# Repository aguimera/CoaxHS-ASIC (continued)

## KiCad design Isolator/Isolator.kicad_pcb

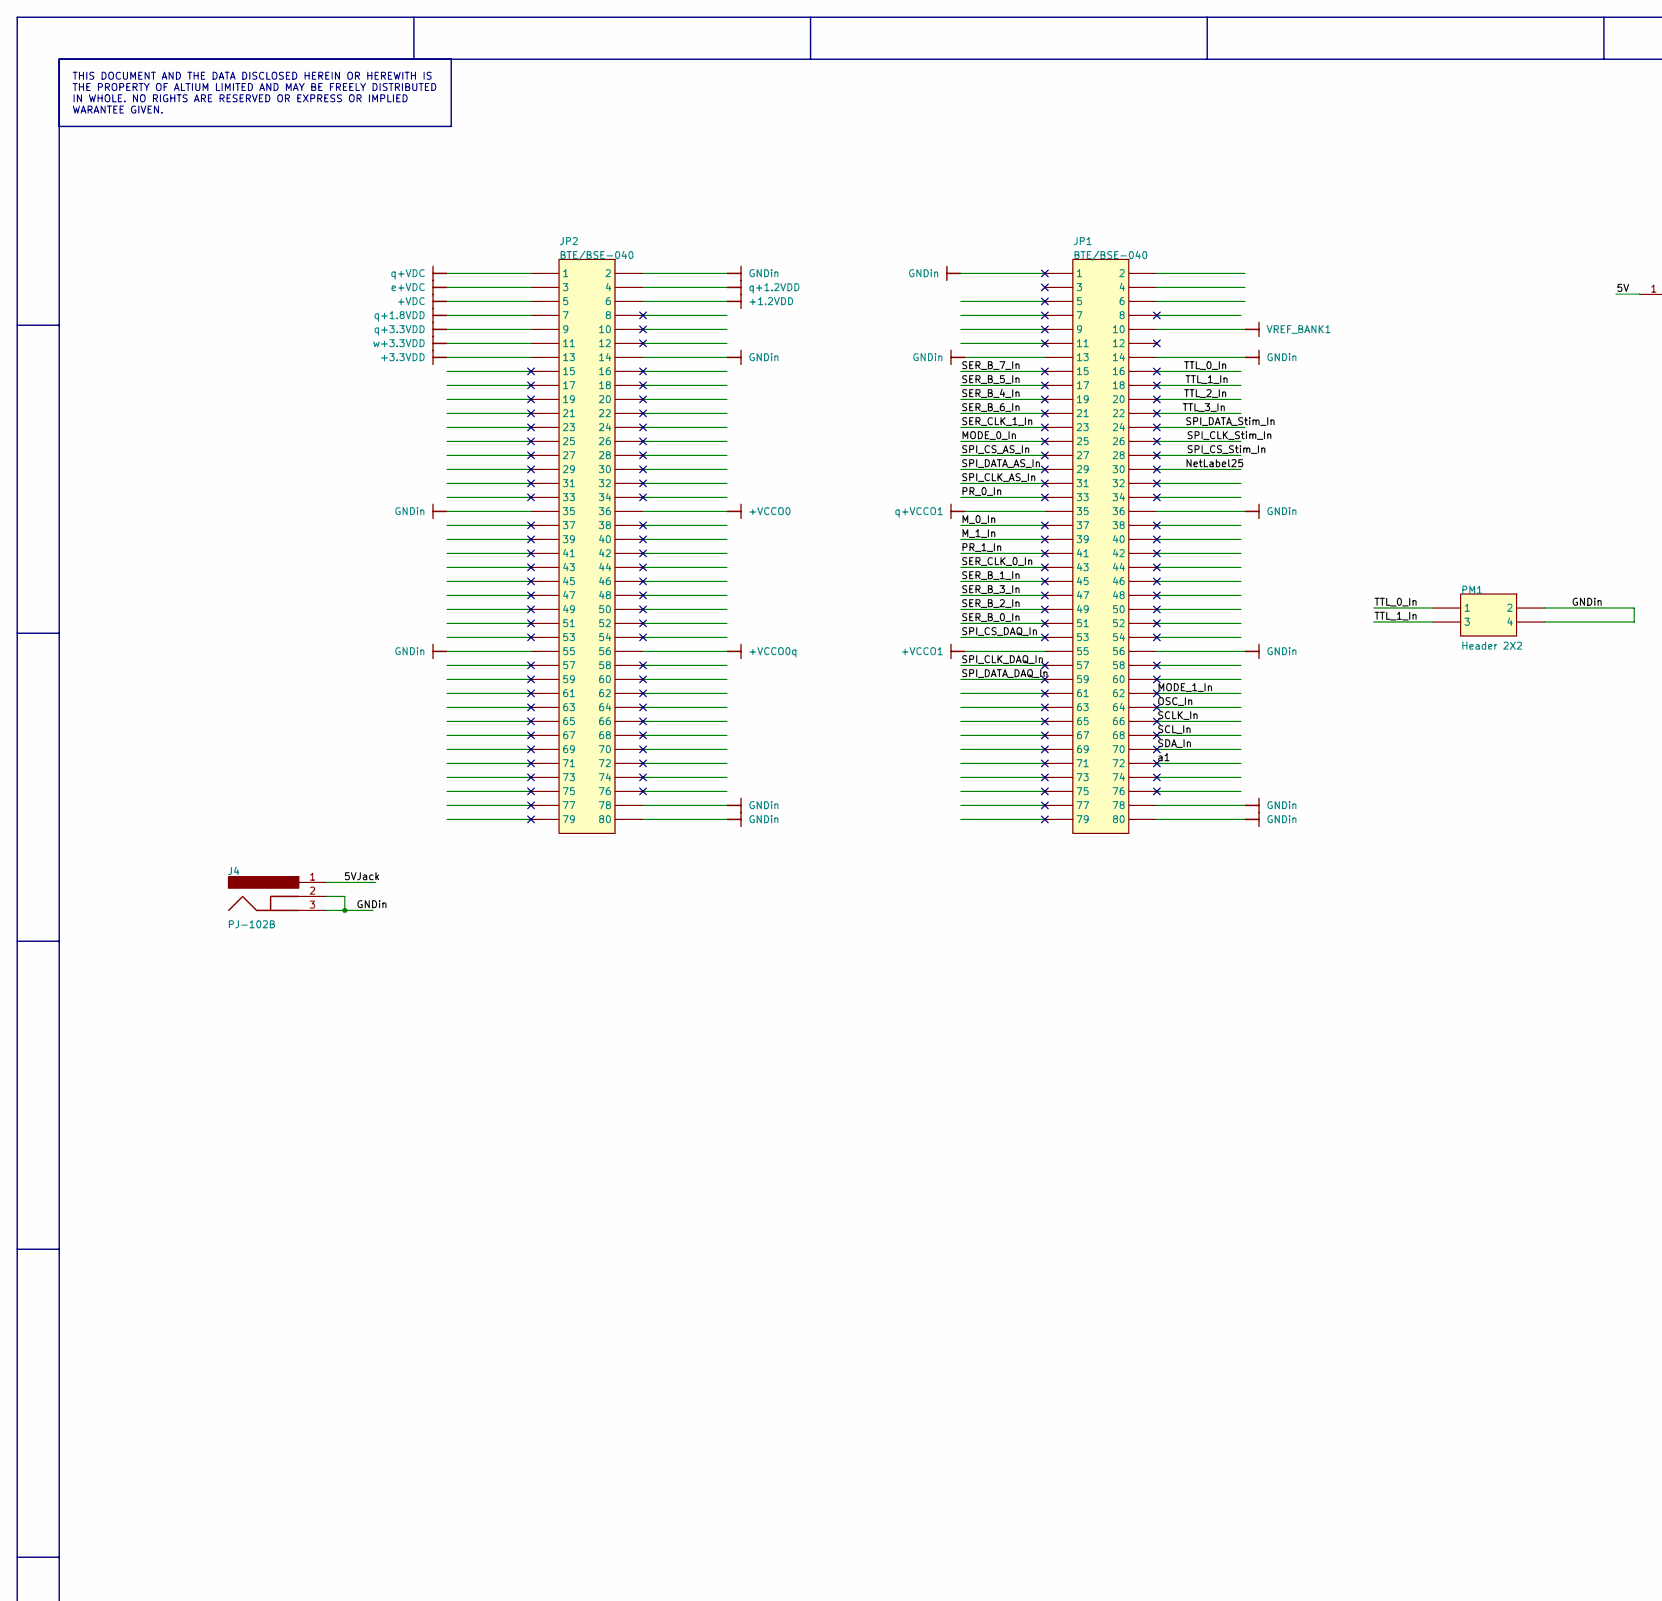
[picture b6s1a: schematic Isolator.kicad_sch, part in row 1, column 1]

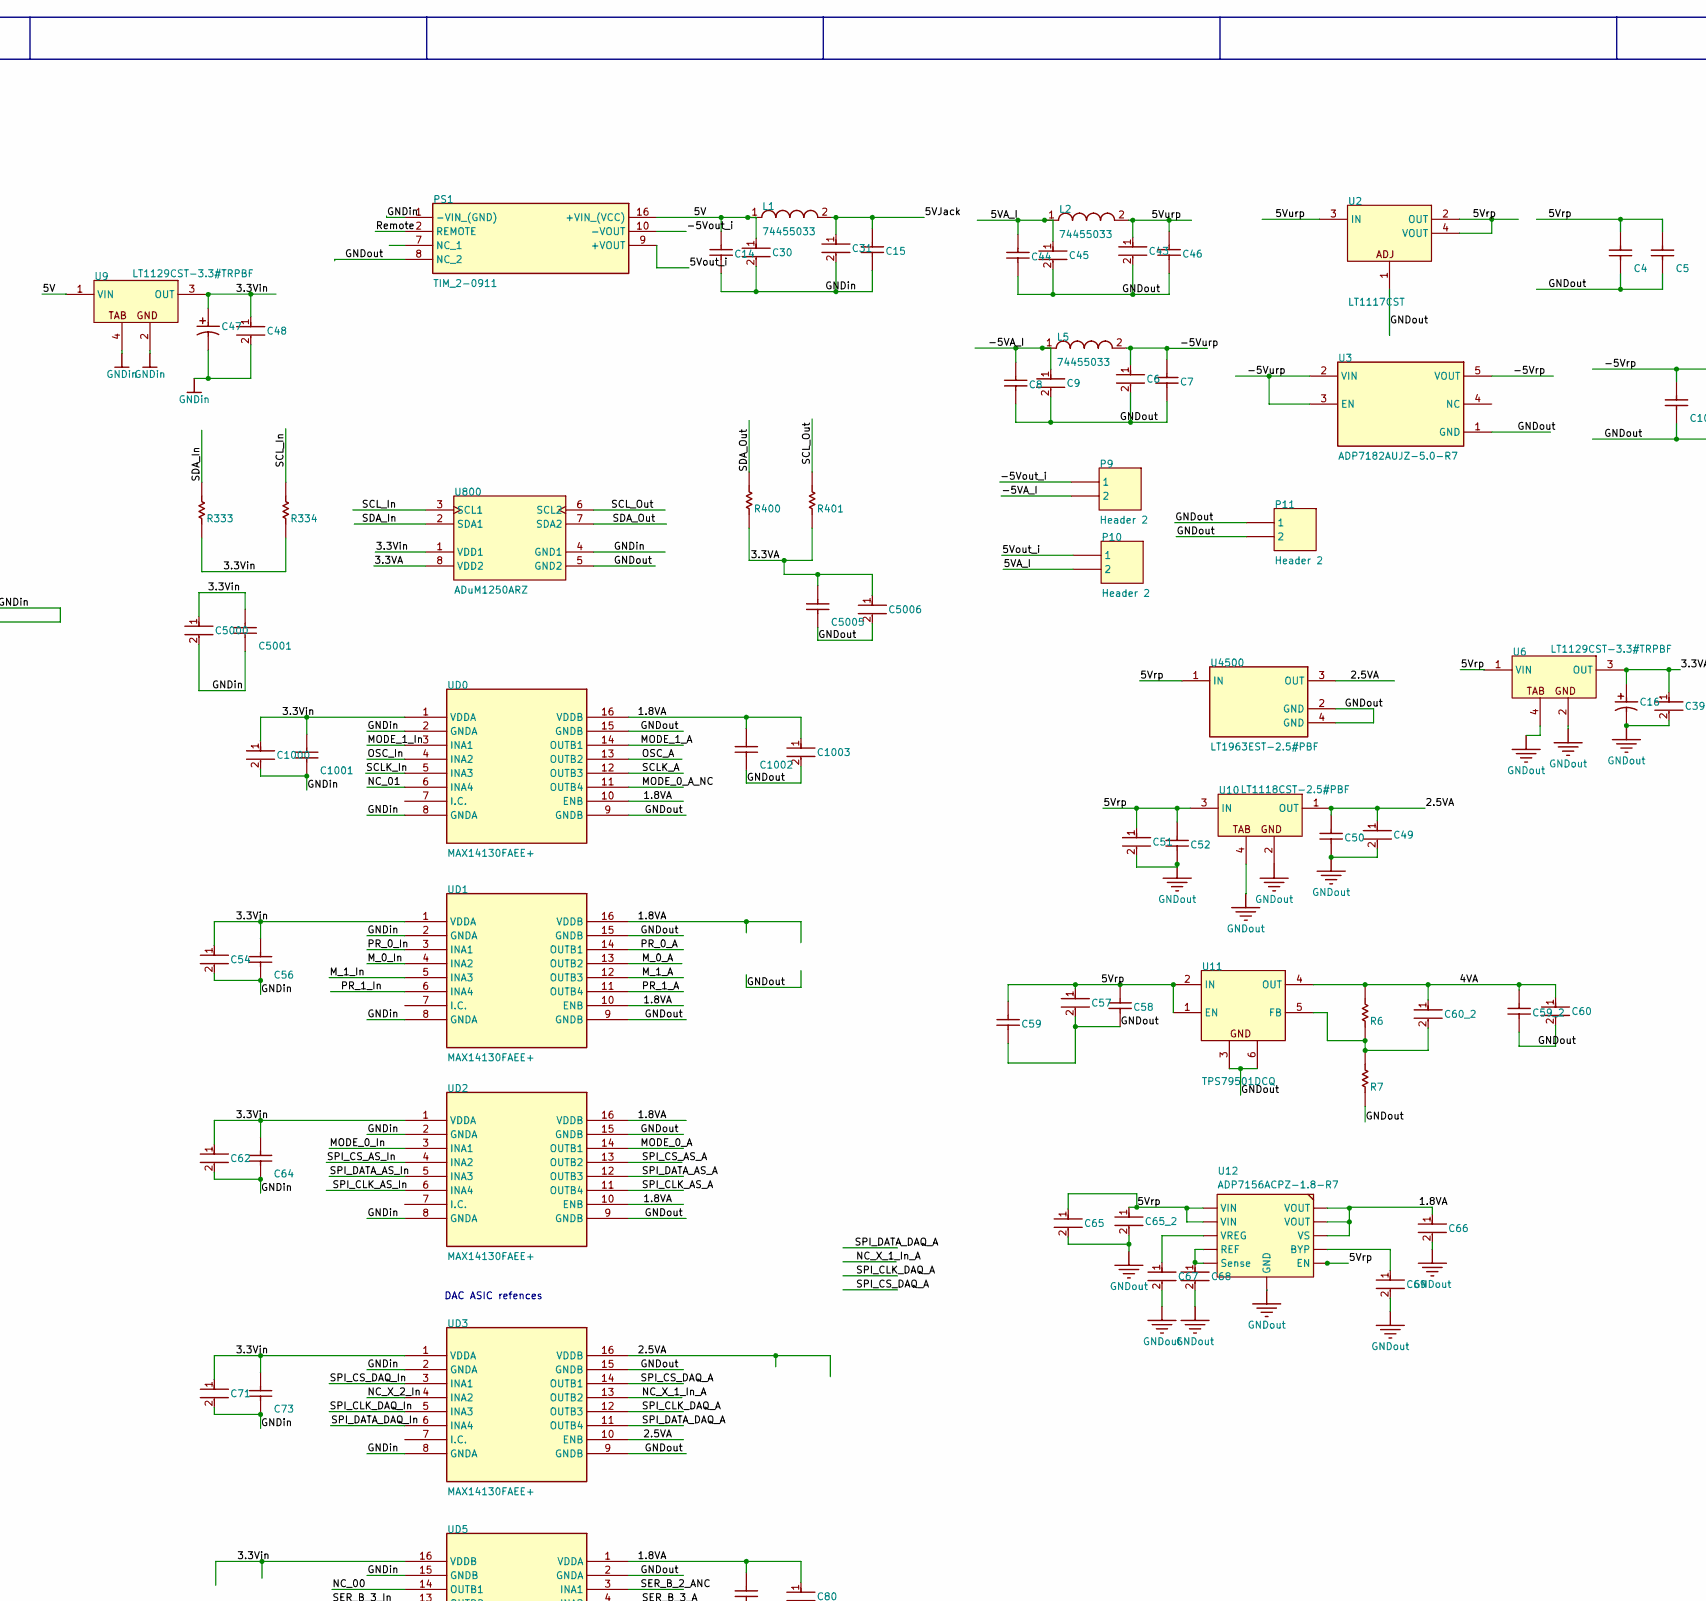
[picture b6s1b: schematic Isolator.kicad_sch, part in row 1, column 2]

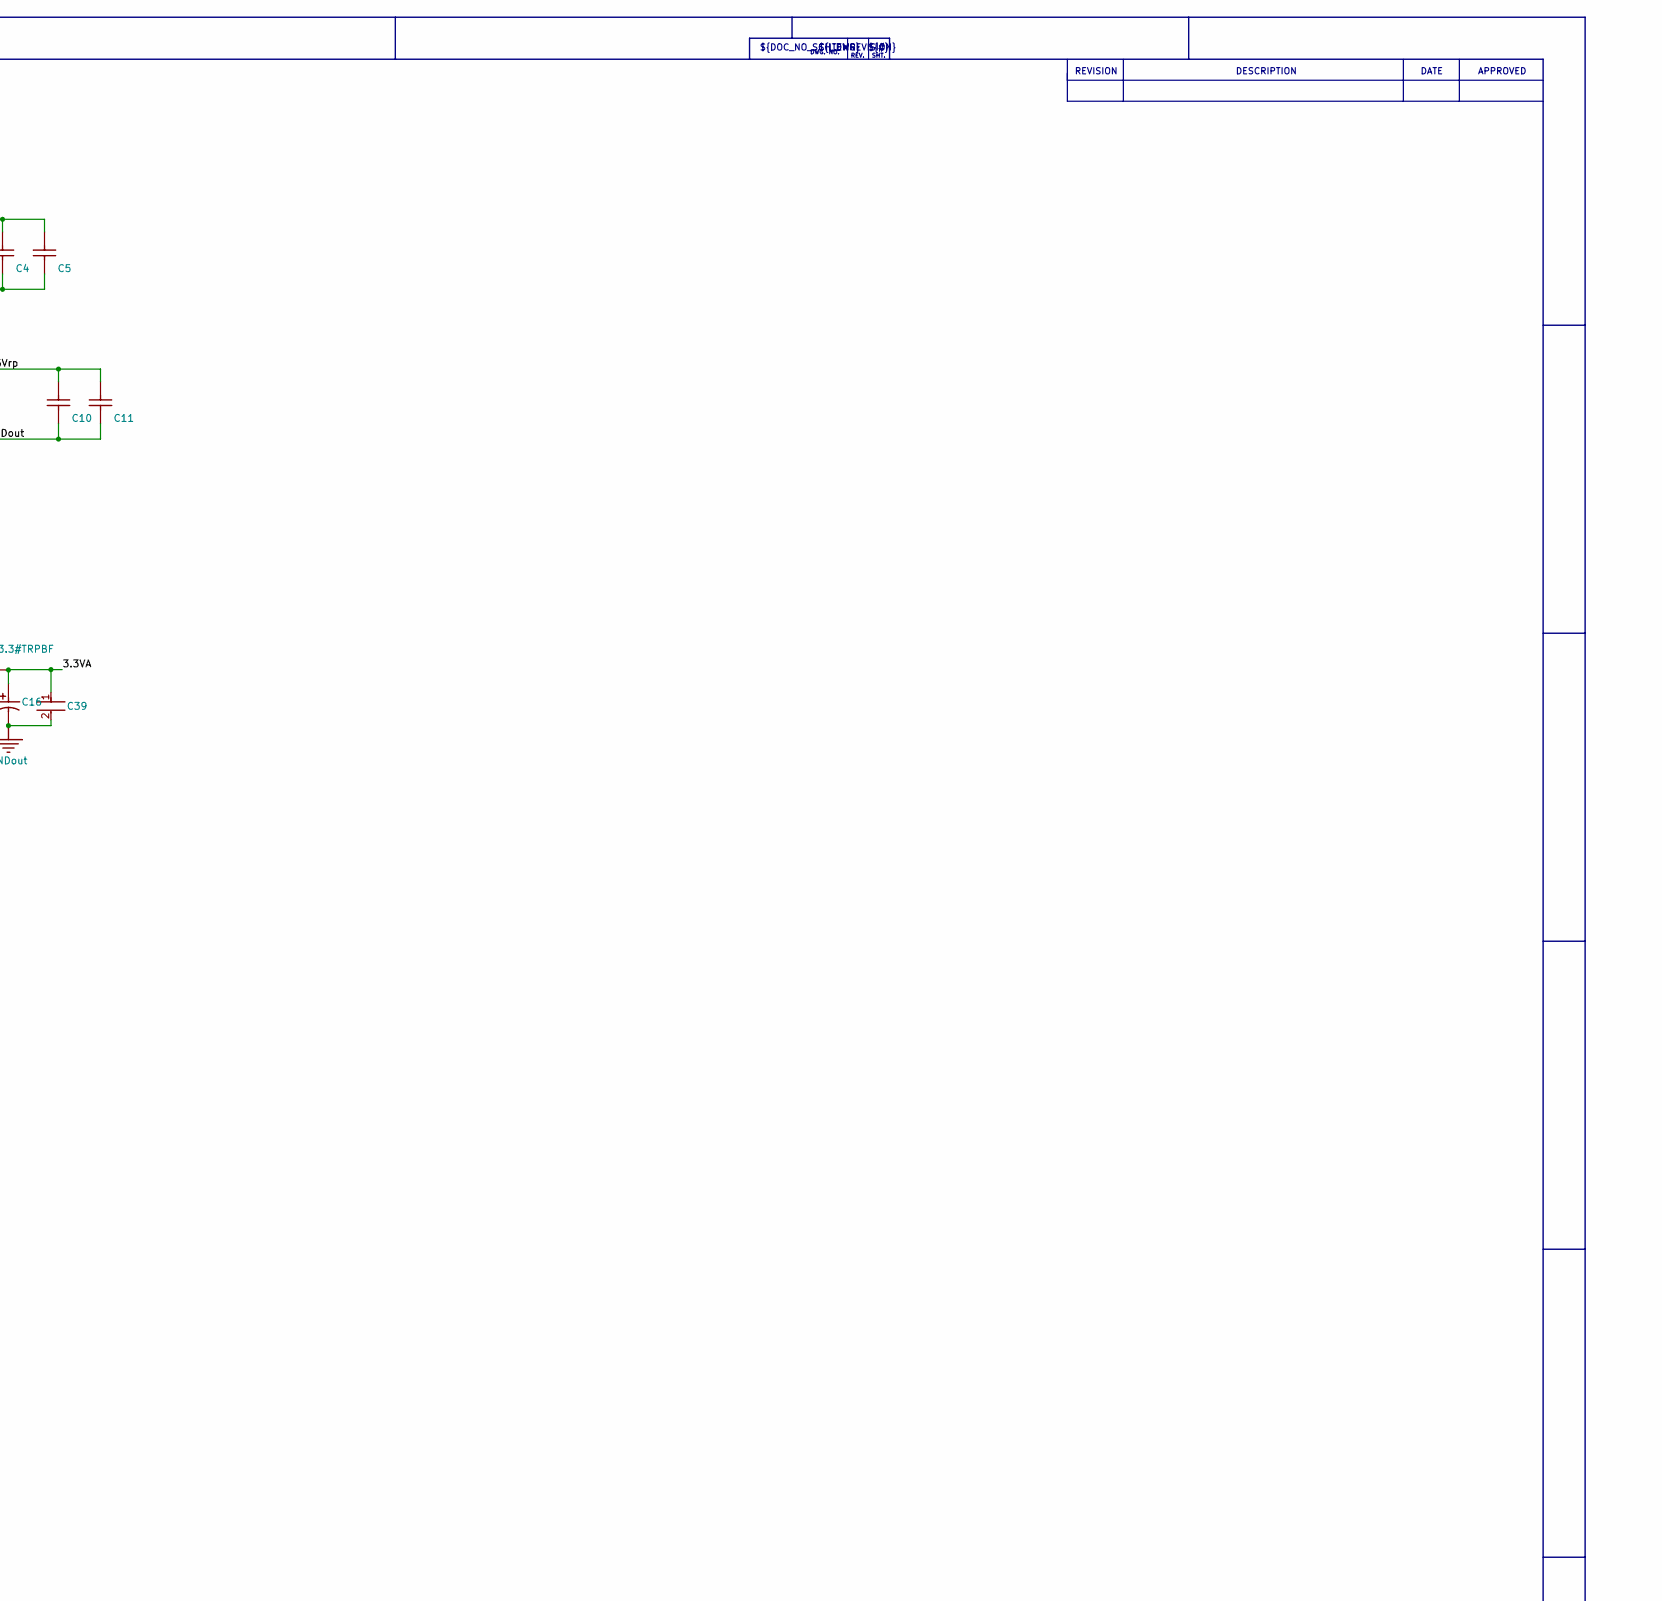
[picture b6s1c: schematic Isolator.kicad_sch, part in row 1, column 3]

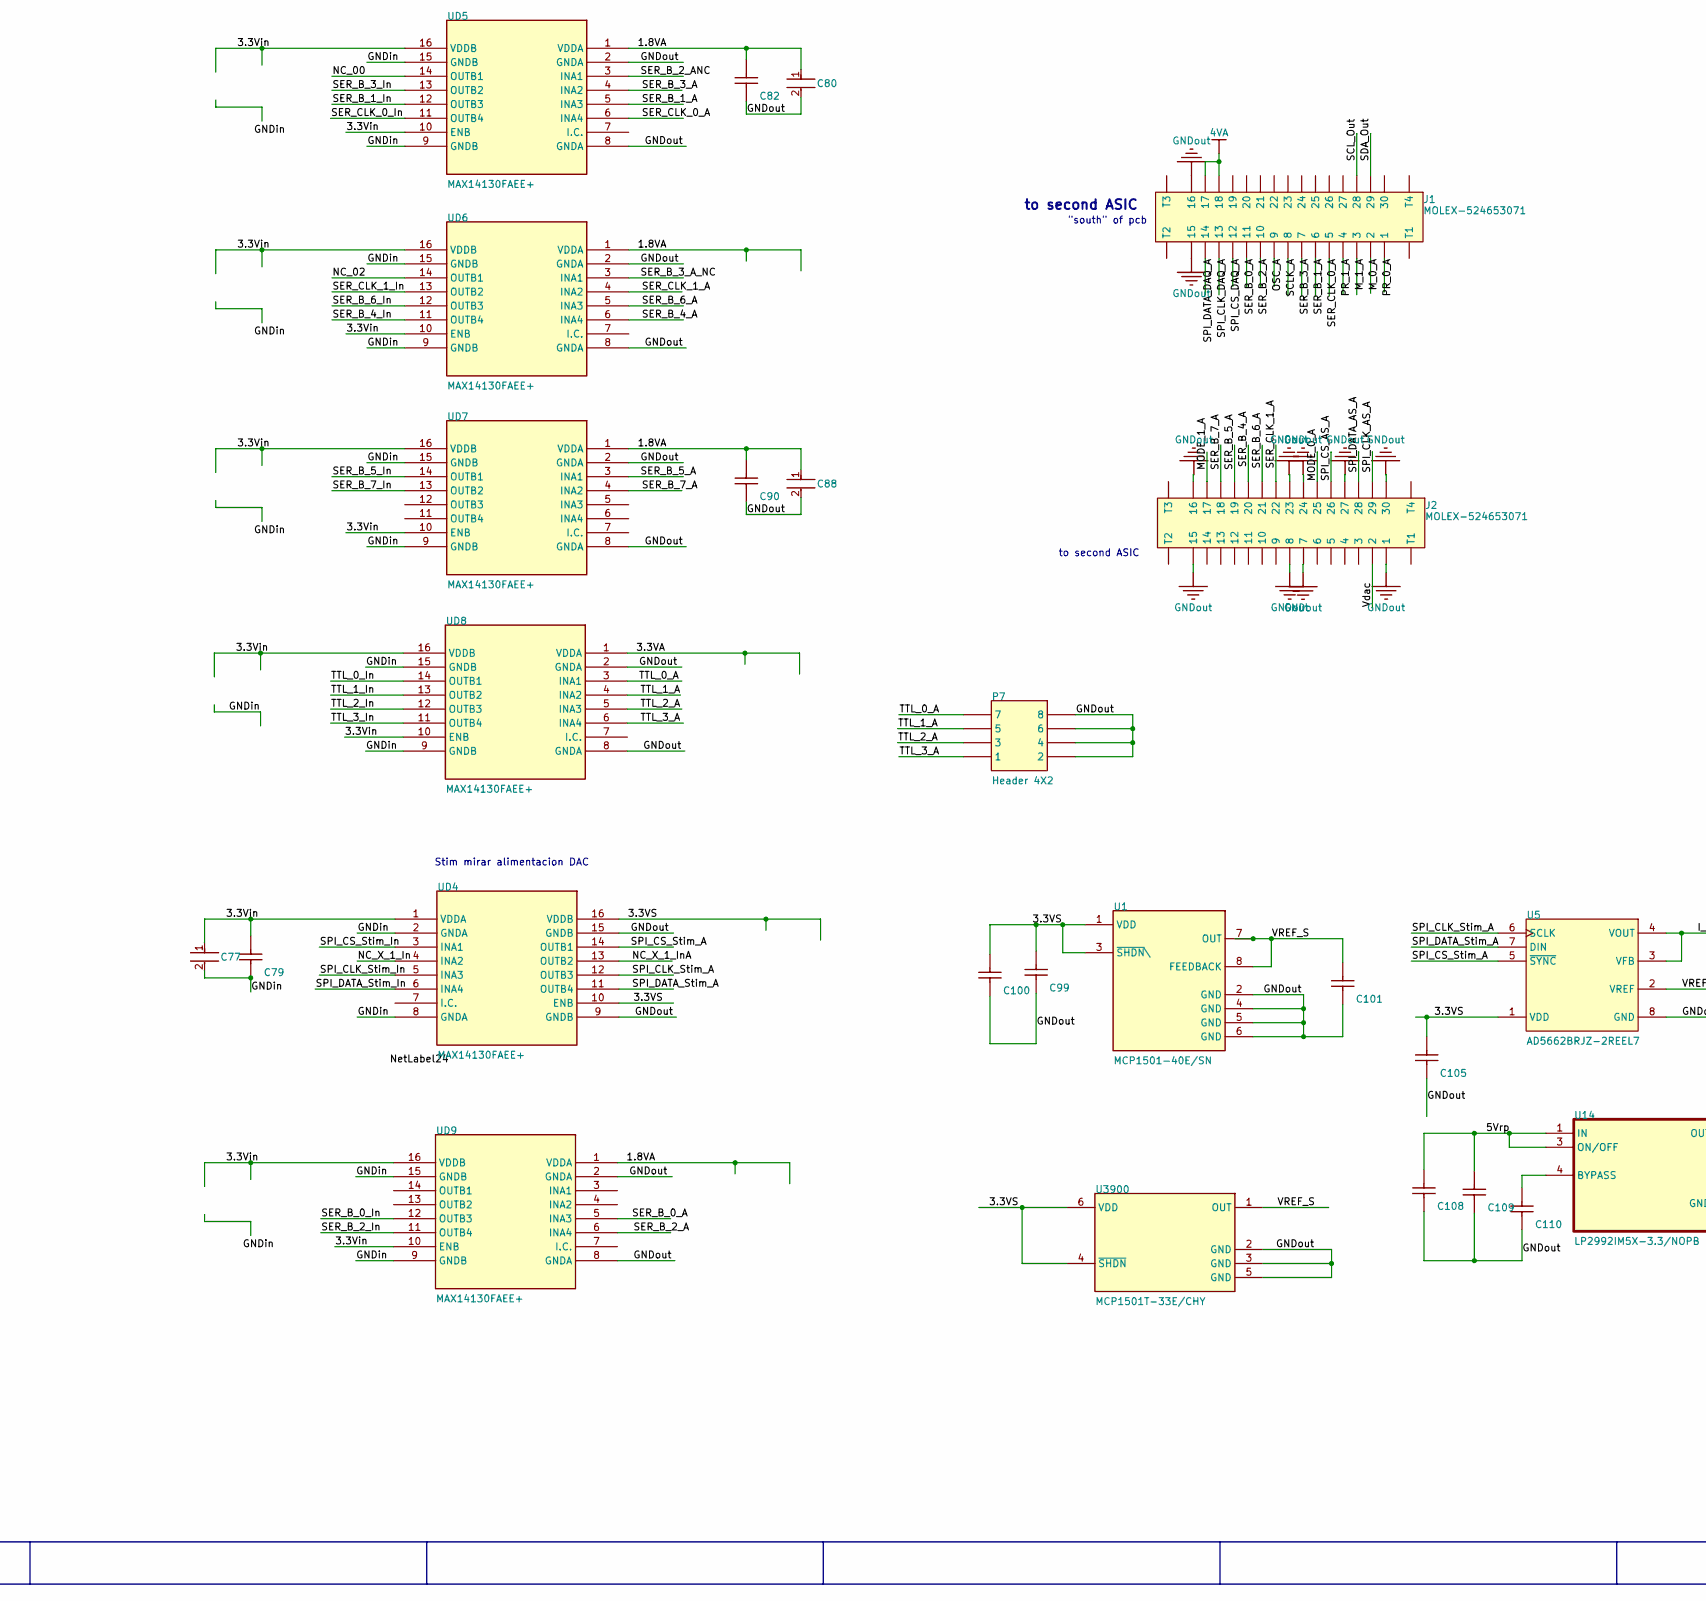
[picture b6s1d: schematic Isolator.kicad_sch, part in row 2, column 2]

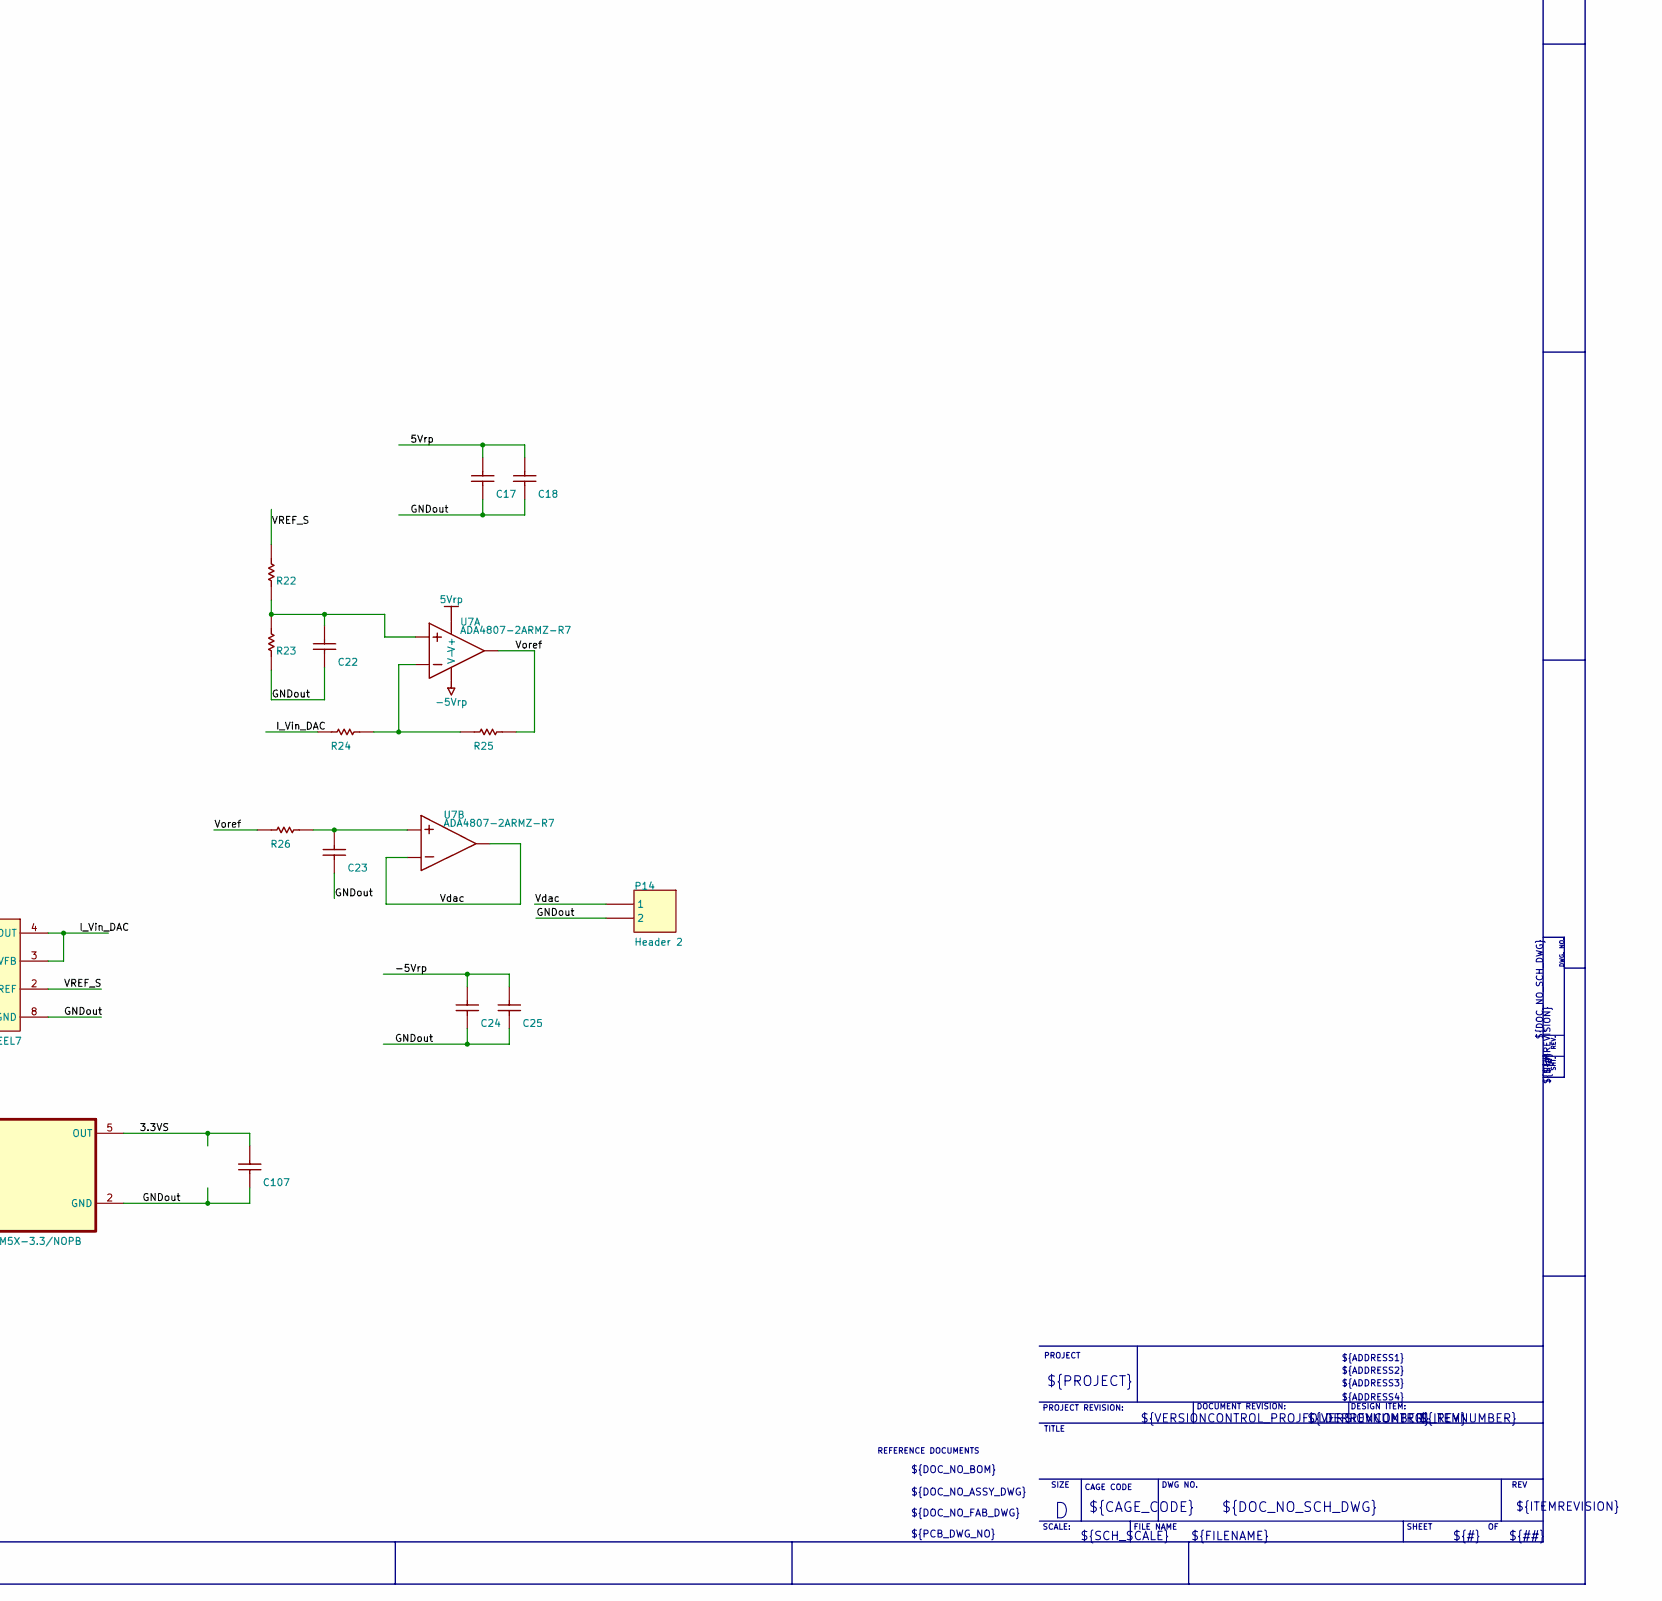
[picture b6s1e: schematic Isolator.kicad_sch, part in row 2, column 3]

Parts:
C4, C5, C10, C11, C17, C18, C24, C25, C56, C64, C73, C79, C82, C90, C99, C100, C101, C105, C107, C108, C109, C110, C1001, C1002, C5001, C5005: 08055C104K4Z2A; CAPC2013X140X50NL20T25; PART NUMBER 08055C104K4Z2A
C6, C9, C30, C31, C39, C43, C45, C48, C49, C51, C54, C57, C60, C60_2, C62, C65, C65_2, C66, C67, C68, C69, C71, C77, C80, C88, C1000, C1003, C5000, C5006: GRM21BR61E106KA73L; FP-GRM21B-0_15-IPC_C; VOLTAGE 25V; VOLTAGE RATING (DC) 25V
C7, C8, C14, C15, C22, C23, C44, C46: GRM32ER61C226KE20L; MURA-1210_H_2.7_L; VOLTAGE RATING DC 16V; TOLERANCE ±10%
C16, C47: T491C105K050AT; KEMT-T491-C_L; TOLERANCE (+ OR -) 10%; VOLTAGE 50VDC
C50, C52, C58: C1206C105K5RACTU; CAPC3216X110X50LL20T25; VOLTAGE RATING 50V; VOLTAGE RATING DC 50V
C59, C59_2: C1210C225K5RACTU; CAPC3225X140X50LL20T25; VOLTAGE RATING 50V; VOLTAGE RATING DC 50V
J1, J2: MOLEX-524653071; J524653071; MPN 524653071
J4: PJ-102B; CUI-PJ-102B_V; VOLTAGE RATING 24V; CURRENT RATING 2.5A
JP1, JP2: BTE/BSE-040; BTE-040; PARTNUMBER 000059
L1, L2, L5: 74455033; WE-PD4-S
P7: Header 4X2; HDR2X4
P9, P10, P11, P14: Header 2; HDR1X2
PM1: Header 2X2; HDR2X2
PS1: TIM_2-0911; TIM20911; MANUFACTURER_PART_NUMBER TIM 2-0911; MOUSER PART NUMBER 495-TIM2-0911
R6, R7, R22, R23, R24, R25, R26, R333, R334, R400, R401: CRCW06030000Z0EA; RESC1609X50X30NL8T20; VOLTAGE RATING 75 V
U1: MCP1501-40E/SN; SOIC127P600X175-8N
U2: LT1117CST; LT-ST-3-SOT-223_M; OUTPUT VOLTAGE Adj; DROPOUT VOLTAGE(V) 1.1; PARTNUMBER LT1117CST
U3: ADP7182AUJZ-5.0-R7; FP-UJ-5-IPC_A; DROPOUT VOLTAGE 185mV; OUTPUT VOLTAGE -5V
U5: AD5662BRJZ-2REEL7; RJ-8_M; PARTNUMBER AD5662BRJZ-2REEL7
U6, U9: LT1129CST-3.3#TRPBF; LT-ST-3-SOT-223_L; DROPOUT VOLTAGE(V) 0.45; OUTPUT VOLTAGE 3.3 V; PARTNUMBER LT1129CST-3.3#TRPBF
U7: ADA4807-2ARMZ-R7; UMSOP8; MPN ADA4807-2ARMZ-R7
U10: LT1118CST-2.5#PBF; LT-ST-3-SOT-223_M; DROPOUT VOLTAGE(V) 1; OUTPUT VOLTAGE 2.5 V; PARTNUMBER LT1118CST-2.5#PBF
U11: TPS79501DCQ; DCQ0006A_N; RATING Catalog; PARTNUMBER TPS79501DCQ
U12: ADP7156ACPZ-1.8-R7; ULFCSP10; MPN ADP7156ACPZ-1.8-R7
U14: LP2992IM5X-3.3/NOPB; SOT95P280X145-5N
U800: ADuM1250ARZ; ADI-R-8_N; SUPPLY VOLTAGE MAX 5.5 V; SUPPLY VOLTAGE MIN 3 V; PARTNUMBER ADuM1250ARZ
U3900: MCP1501T-33E/CHY; FP-C04-028-IPC_A; TOLERANCE 0.08%
U4500: LT1963EST-2.5#PBF; FP-ST-3-05-08-1630-IPC_A; DROPOUT VOLTAGE 340mV; OUTPUT VOLTAGE 2.5V
UD0, UD1, UD2, UD3, UD4, UD5, UD6, UD7, UD8, UD9: MAX14130FAEE+; SOP63P602X175-16N; MANUFACTURER_PART_NUMBER MAX14130FAEE+

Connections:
4VA: C59_2.2, C60.1, C60_2.1, J1.17, J1.18, R6.2, U11.4 (OUT)
5Vrp: C4.1, C5.1, C17.1, C18.1, C51.1, C52.2, C57.1, C58.2, C59.2, C65.1, C65_2.1, C108.1, C109.1, U2.2 (OUT), U2.4 (VOUT), U6.1 (VIN), U7.8 (V+), U10.3 (IN), U11.1 (EN), U11.2 (IN), U12.5 (EN), U12.9 (VIN), U12.10 (VIN), U14.1 (IN), U14.3 (ON/OFF), U4500.1 (IN)
+1.2VDD: JP2.6
+3.3VDD: JP2.13
+VCCO0: JP2.36
+VCCO0q: JP2.56
+VCCO1: JP1.55
+VDC: JP2.5
-5Vrp: C10.1, C11.1, C24.1, C25.1, U3.5 (VOUT), U7.4 (V-)
/1.8VA: C66.1, C80.1, C82.1, C88.1, C90.1, C1002.1, C1003.1, U12.1 (VOUT), U12.2 (VOUT), U12.3 (VS), UD0.10 (ENB), UD0.16 (VDDB), UD1.10 (ENB), UD1.16 (VDDB), UD2.10 (ENB), UD2.16 (VDDB), UD5.1 (VDDA), UD6.1 (VDDA), UD7.1 (VDDA), UD9.1 (VDDA)
/2.5VA: C49.1, C50.2, U10.1 (OUT), U4500.3 (OUT), UD3.10 (ENB), UD3.16 (VDDB)
/3.3VA: C16.1, C39.1, C5005.1, C5006.1, R400.1, R401.1, U6.3 (OUT), U800.8 (VDD2), UD8.1 (VDDA)
/3.3VS: C99.1, C100.1, C105.1, C107.1, U1.1 (VDD), U1.3 (~SHDN\), U5.1 (VDD), U14.5 (OUT), U3900.4 (~SHDN), U3900.6 (VDD), UD4.10 (ENB), UD4.16 (VDDB)
/3.3Vin: C47.1, C48.1, C54.1, C56.1, C62.1, C64.1, C71.1, C73.1, C77.1, C79.1, C1000.1, C1001.1, C5000.1, C5001.1, R333.1, R334.1, U9.3 (OUT), U800.1 (VDD1), UD0.1 (VDDA), UD1.1 (VDDA), UD2.1 (VDDA), UD3.1 (VDDA), UD4.1 (VDDA), UD5.10 (ENB), UD5.16 (VDDB), UD6.10 (ENB), UD6.16 (VDDB), UD7.10 (ENB), UD7.16 (VDDB), UD8.10 (ENB), UD8.16 (VDDB), UD9.10 (ENB), UD9.16 (VDDB)
/5V: C14.2, C30.1, L1.1, PS1.16 (+VIN_(VCC)), U9.1 (VIN)
/5VA_I: C44.2, C45.1, L2.1, P10.2
/5VJack: C15.2, C31.1, J4.1, L1.2
/5Vout_i: P10.1, PS1.9 (+VOUT)
/5Vurp: C43.1, C46.2, L2.2, U2.3 (IN)
/-5VA_I: C8.2, C9.1, L5.1, P9.2
/-5Vout_i: P9.1, PS1.10 (-VOUT)
/-5Vurp: C6.1, C7.2, L5.2, U3.2 (VIN), U3.3 (EN)
/I_Vin_DAC: R24.2, U5.3 (VFB), U5.4 (VOUT)
/MODE_0_A: J2.25, UD2.14 (OUTB1)
/MODE_0_A_NC: UD0.11 (OUTB4)
/MODE_0_In: JP1.25, UD2.3 (INA1)
/MODE_1_A: J2.17, UD0.14 (OUTB1)
/MODE_1_In: JP1.62, UD0.3 (INA1)
/M_0_A: J1.2, UD1.13 (OUTB2)
/M_0_In: JP1.37, UD1.4 (INA2)
/M_1_A: J1.3, UD1.12 (OUTB3)
/M_1_In: JP1.39, UD1.5 (INA3)
/NC_00: UD5.14 (OUTB1)
/NC_01: UD0.6 (INA4)
/NC_02: UD6.14 (OUTB1)
/NC_X_1_In: UD4.4 (INA2)
/NC_X_1_InA: UD4.13 (OUTB2)
/NC_X_1_In_A: UD3.13 (OUTB2)
/NC_X_2_In: UD3.4 (INA2)
/NetLabel25: JP1.30
/OSC_A: J1.9, UD0.13 (OUTB2)
/OSC_In: JP1.64, UD0.4 (INA2)
/PR_0_A: J1.1, UD1.14 (OUTB1)
/PR_0_In: JP1.33, UD1.3 (INA1)
/PR_1_A: J1.4, UD1.11 (OUTB4)
/PR_1_In: JP1.41, UD1.6 (INA4)
/Remote: PS1.2 (REMOTE)
/SCLK_A: J1.8, UD0.12 (OUTB3)
/SCLK_In: JP1.66, UD0.5 (INA3)
/SCL_In: JP1.68, R334.2, U800.3 (SCL1)
/SCL_Out: J1.28, R401.2, U800.6 (SCL2)
/SDA_In: JP1.70, R333.2, U800.2 (SDA1)
/SDA_Out: J1.29, R400.2, U800.7 (SDA2)
/SER_B_0_A: J1.11, UD9.5 (INA3)
/SER_B_0_In: JP1.51, UD9.12 (OUTB3)
/SER_B_1_A: J1.6, UD5.5 (INA3)
/SER_B_1_In: JP1.45, UD5.12 (OUTB3)
/SER_B_2_A: J1.10, UD9.6 (INA4)
/SER_B_2_ANC: UD5.3 (INA1)
/SER_B_2_In: JP1.49, UD9.11 (OUTB4)
/SER_B_3_A: J1.7, UD5.4 (INA2)
/SER_B_3_A_NC: UD6.3 (INA1)
/SER_B_3_In: JP1.47, UD5.13 (OUTB2)
/SER_B_4_A: J2.20, UD6.6 (INA4)
/SER_B_4_In: JP1.19, UD6.11 (OUTB4)
/SER_B_5_A: J2.19, UD7.3 (INA1)
/SER_B_5_In: JP1.17, UD7.14 (OUTB1)
/SER_B_6_A: J2.21, UD6.5 (INA3)
/SER_B_6_In: JP1.21, UD6.12 (OUTB3)
/SER_B_7_A: J2.18, UD7.4 (INA2)
/SER_B_7_In: JP1.15, UD7.13 (OUTB2)
/SER_CLK_0_A: J1.5, UD5.6 (INA4)
/SER_CLK_0_In: JP1.43, UD5.11 (OUTB4)
/SER_CLK_1_A: J2.22, UD6.4 (INA2)
/SER_CLK_1_In: JP1.23, UD6.13 (OUTB2)
/SPI_CLK_AS_A: J2.29, UD2.11 (OUTB4)
/SPI_CLK_AS_In: JP1.31, UD2.6 (INA4)
/SPI_CLK_DAQ_A: J1.13, UD3.12 (OUTB3)
/SPI_CLK_DAQ_In: JP1.57, UD3.5 (INA3)
/SPI_CLK_Stim_A: U5.6 (SCLK), UD4.12 (OUTB3)
/SPI_CLK_Stim_In: JP1.26, UD4.5 (INA3)
/SPI_CS_AS_A: J2.26, UD2.13 (OUTB2)
/SPI_CS_AS_In: JP1.27, UD2.4 (INA2)
/SPI_CS_DAQ_A: J1.12, UD3.14 (OUTB1)
/SPI_CS_DAQ_In: JP1.53, UD3.3 (INA1)
/SPI_CS_Stim_A: U5.5 (~SYNC), UD4.14 (OUTB1)
/SPI_CS_Stim_In: JP1.28, UD4.3 (INA1)
/SPI_DATA_AS_A: J2.28, UD2.12 (OUTB3)
/SPI_DATA_AS_In: JP1.29, UD2.5 (INA3)
/SPI_DATA_DAQ_A: J1.14, UD3.11 (OUTB4)
/SPI_DATA_DAQ_In: JP1.59, UD3.6 (INA4)
/SPI_DATA_Stim_A: U5.7 (DIN), UD4.11 (OUTB4)
/SPI_DATA_Stim_In: JP1.24, UD4.6 (INA4)
/TTL_0_A: P7.7, UD8.3 (INA1)
/TTL_0_In: JP1.16, PM1.1, UD8.14 (OUTB1)
/TTL_1_A: P7.5, UD8.4 (INA2)
/TTL_1_In: JP1.18, PM1.3, UD8.13 (OUTB2)
/TTL_2_A: P7.3, UD8.5 (INA3)
/TTL_2_In: JP1.20, UD8.12 (OUTB3)
/TTL_3_A: P7.1, UD8.6 (INA4)
/TTL_3_In: JP1.22, UD8.11 (OUTB4)
/VREF_S: C101.1, R22.2, U1.7 (OUT), U1.8 (FEEDBACK), U5.2 (VREF), U3900.1 (OUT)
/Vdac: J2.2, P14.1, U7.6 (IN2), U7.7 (OUT)
/Voref: R25.1, R26.2, U7.1 (OUT)
/a1: JP1.72
GNDin: C14.1, C15.1, C30.2, C31.2, C47.2, C48.2, C54.2, C56.2, C62.2, C64.2, C71.2, C73.2, C77.2, C79.2, C1000.2, C1001.2, C5000.2, C5001.2, J4.2, J4.3, JP1.1, JP1.13, JP1.14, JP1.36, JP1.56, JP1.78, JP1.80, JP2.2, JP2.14, JP2.35, JP2.55, JP2.78, JP2.80, PM1.2, PM1.4, PS1.1 (-VIN_(GND)), U9.2 (GND), U9.4 (TAB), U800.4 (GND1), UD0.2 (GNDA), UD0.8 (GNDA), UD1.2 (GNDA), UD1.8 (GNDA), UD2.2 (GNDA), UD2.8 (GNDA), UD3.2 (GNDA), UD3.8 (GNDA), UD4.2 (GNDA), UD4.8 (GNDA), UD5.9 (GNDB), UD5.15 (GNDB), UD6.9 (GNDB), UD6.15 (GNDB), UD7.9 (GNDB), UD7.15 (GNDB), UD8.9 (GNDB), UD8.15 (GNDB), UD9.9 (GNDB), UD9.15 (GNDB)
GNDout: C4.2, C5.2, C6.2, C7.1, C8.1, C9.2, C10.2, C11.2, C16.2, C17.2, C18.2, C22.2, C23.2, C24.2, C25.2, C39.2, C43.2, C44.1, C45.2, C46.1, C49.2, C50.1, C51.2, C52.1, C57.2, C58.1, C59.1, C59_2.1, C60.2, C65.2, C65_2.2, C66.2, C67.2, C68.2, C69.2, C80.2, C82.2, C88.2, C90.2, C99.2, C100.2, C101.2, C105.2, C107.2, C108.2, C109.2, C110.2, C1002.2, C1003.2, C5005.2, C5006.2, J1.15, J1.16, J2.1, J2.7, J2.8, J2.15, J2.16, J2.23, J2.24, J2.27, J2.30, P7.2, P7.4, P7.6, P7.8, P11.1, P11.2, P14.2, PS1.8 (NC_2), R7.1, R23.1, U1.2 (GND), U1.4 (GND), U1.5 (GND), U1.6 (GND), U2.1 (ADJ), U3.1 (GND), U5.8 (GND), U6.2 (GND), U6.4 (TAB), U10.2 (GND), U10.4 (TAB), U11.3 (GND), U11.6 (GND), U12.0 (GND), U14.2 (GND), U800.5 (GND2), U3900.2 (GND), U3900.3 (GND), U3900.5 (GND), U4500.2 (GND), U4500.4 (GND), UD0.9 (GNDB), UD0.15 (GNDB), UD1.9 (GNDB), UD1.15 (GNDB), UD2.9 (GNDB), UD2.15 (GNDB), UD3.9 (GNDB), UD3.15 (GNDB), UD4.9 (GNDB), UD4.15 (GNDB), UD5.2 (GNDA), UD5.8 (GNDA), UD6.2 (GNDA), UD6.8 (GNDA), UD7.2 (GNDA), UD7.8 (GNDA), UD8.2 (GNDA), UD8.8 (GNDA), UD9.2 (GNDA), UD9.8 (GNDA)
unnamed: C22.1, R22.1, R23.2, U7.3 (+IN)
unnamed: R24.1, R25.2, U7.2 (-IN)
unnamed: C23.1, R26.1, U7.5 (+IN2)
unnamed: C60_2.2, R6.1, R7.2, U11.5 (FB)
unnamed: C69.1, U12.4 (BYP)
unnamed: C68.1, U12.6 (Sense), U12.7 (REF)
unnamed: C67.1, U12.8 (VREG)
unnamed: C110.1, U14.4 (BYPASS)
VREF_BANK1: JP1.10
e+VDC: JP2.3
q+1.2VDD: JP2.4
q+1.8VDD: JP2.7
q+3.3VDD: JP2.9
q+VCCO1: JP1.35
q+VDC: JP2.1
w+3.3VDD: JP2.11

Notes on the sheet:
THIS DOCUMENT AND THE DATA DISCLOSED HEREIN OR HEREWITH IS THE PROPERTY OF ALTIUM LIMITED AND MAY BE FREELY DISTRIBUTED IN WHOLE. NO RIGHTS ARE RESERVED OR EXPRESS OR IMPLIED WARANTEE GIVEN.
TITLE
DESCRIPTION
REV.
SHEET
${#}
SHT.
PROJECT REVISION:
CAGE CODE
SIZE
REFERENCE DOCUMENTS
${DOC_NO_SCH_DWG}
${PROJECT}
${FILENAME}
Stim mirar alimentacion DAC
DAC ASIC refences
${DOC_NO_FAB_DWG}
${ADDRESS3}
DWG NO.
${CAGE_CODE}
DESIGN ITEM:
${TITLE}
to second ASIC
FILE NAME
${ITEMREVISION}
${DOC_NO_BOM}
${ADDRESS4}
DWG. NO.
REV
${SCH_SCALE}
${VERSIONCONTROL_PROJFOLDERREVNUMBER}
DOCUMENT REVISION:
SCALE:
${ADDRESS2}
${ADDRESS1}
${VERSIONCONTROL_REVNUMBER}
${PCB_DWG_NO}
${DOC_NO_ASSY_DWG}
DATE
${##}

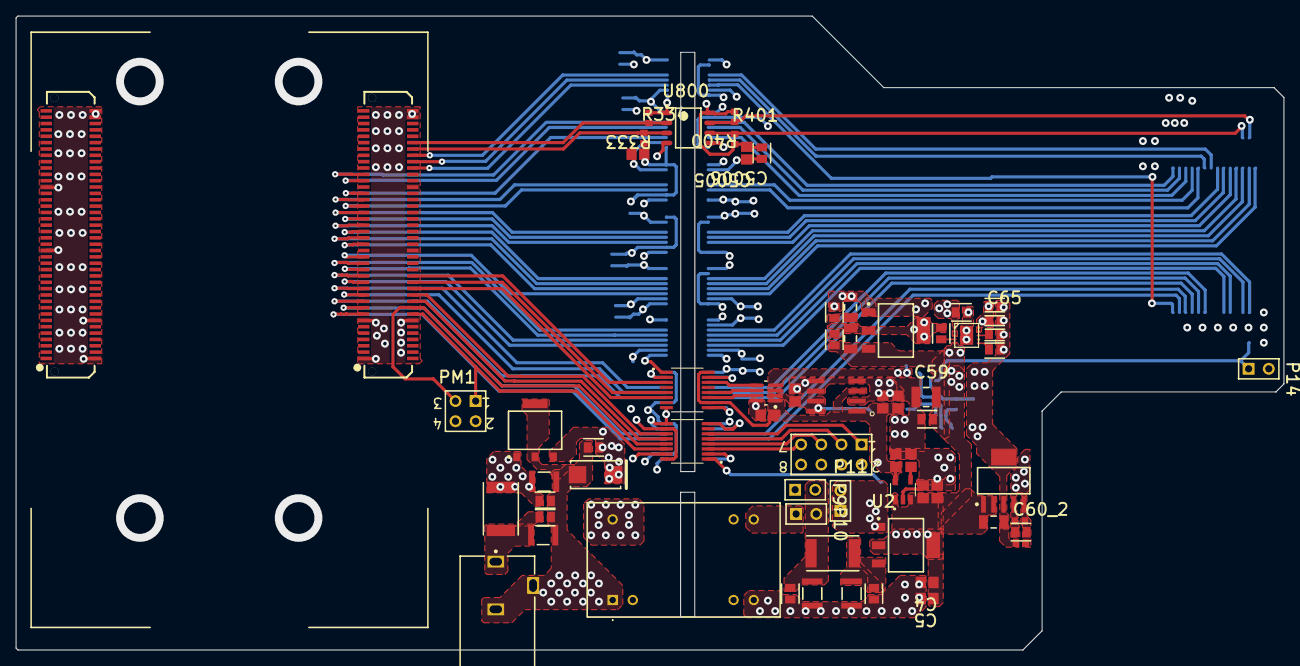
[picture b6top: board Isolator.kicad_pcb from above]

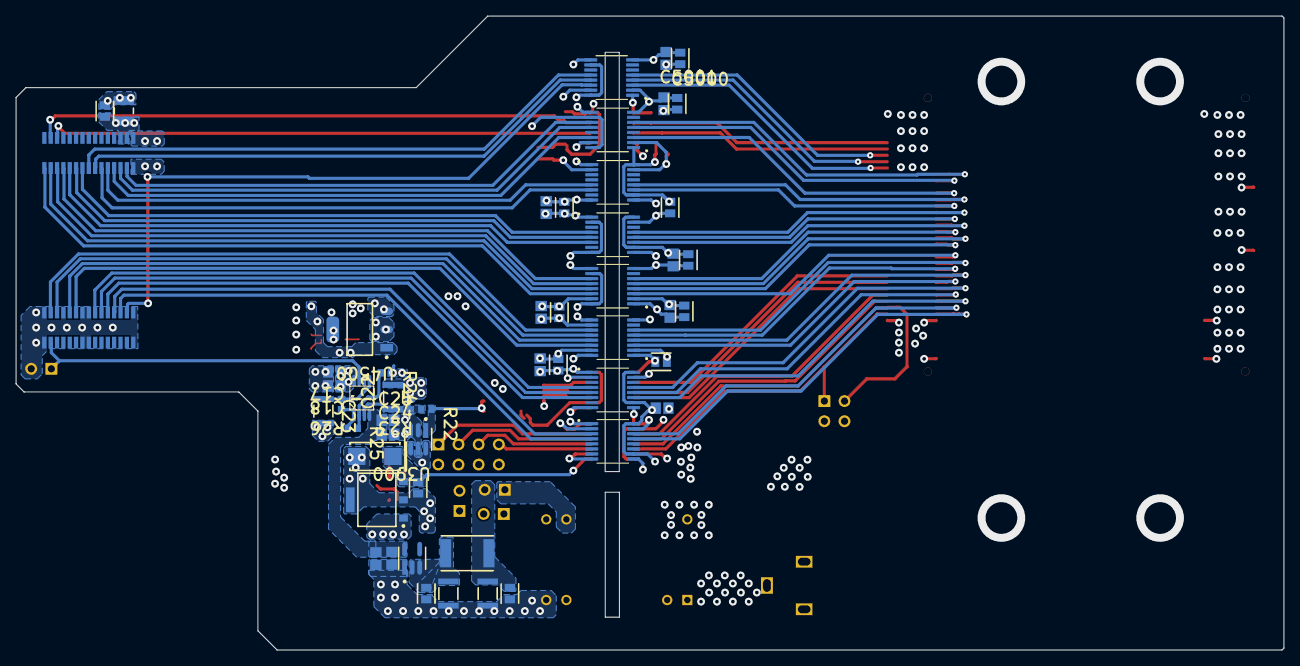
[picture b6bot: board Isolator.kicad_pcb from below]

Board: 4 copper layers, 159.8 x 79.9 mm, 120 parts (54 on the bottom side), 96 nets.
